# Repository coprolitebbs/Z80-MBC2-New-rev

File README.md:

# Z80-MBC2-New-rev
New revision of computer Z80-MBC2

4 blocks and Mainboard

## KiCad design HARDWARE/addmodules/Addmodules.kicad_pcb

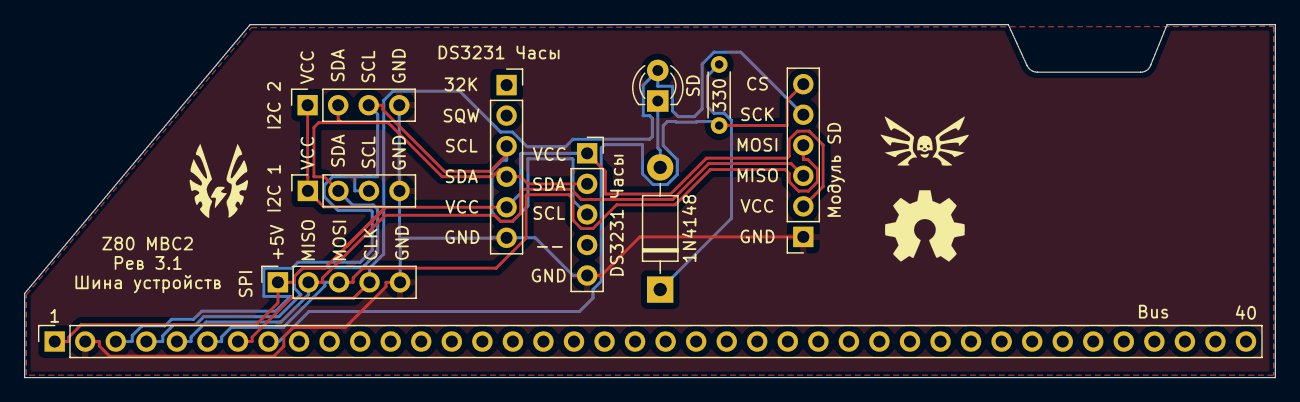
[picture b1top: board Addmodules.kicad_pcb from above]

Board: 2 copper layers, 104.0 x 29.3 mm, 10 parts (0 on the bottom side), 10 nets.

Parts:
D1: 1N4148; D_DO-41_SOD81_P10.16mm_Horizontal
D2: SD; LED_D3.0mm
J1: DS3231 Часы; PinSocket_1x06_P2.54mm_Vertical_RTC
J2: Модуль SD; PinSocket_1x06_P2.54mm_Vertical_SD
J3: DS3231 Часы; PinSocket_1x05_P2.54mm_Vertical
J4: I2C 1; PinSocket_1x04_P2.54mm_Vertical_I2C
J5: I2C 2; PinSocket_1x04_P2.54mm_Vertical_I2C
J6: SPI; PinSocket_1x05_P2.54mm_Vertical
J10: Bus; PinSocket_1x40_P2.54mm_Vertical
R1: 330; R_Axial_DIN0204_L3.6mm_D1.6mm_P5.08mm_Horizontal

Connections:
+5V: J1.5, J2.2, J3.1, J4.1, J5.1, J6.1, J10.1
CSK: D2.2 (A), J2.5, J6.4, J10.7
GND: J1.6, J2.1, J3.5, J4.4, J5.4, J6.5, J10.2
MISO: J2.3, J6.2, J10.5
MOSI: J2.4, J6.3, J10.6
unnamed: D1.1 (A), R1.1
unnamed: D1.2 (K), D2.1 (K)
SCL: J1.3, J3.3, J4.3, J5.3, J10.3
SDA: J1.4, J3.2, J4.2, J5.2, J10.4
SS: J2.6, J10.8, R1.2

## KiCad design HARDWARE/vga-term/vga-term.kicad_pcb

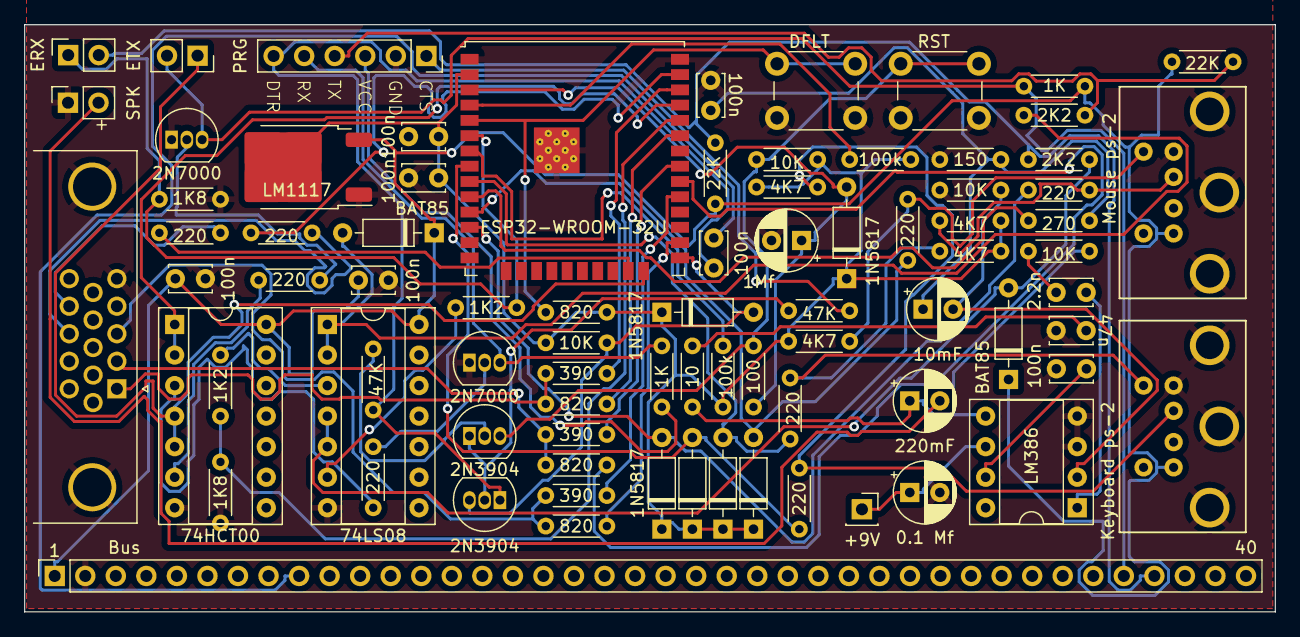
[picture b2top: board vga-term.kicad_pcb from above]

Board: 2 copper layers, 104.0 x 48.8 mm, 82 parts (0 on the bottom side), 62 nets.

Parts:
C1-nn1, C2, C3, C4, C5, C6, C11: 100n; C_Disc_D3.4mm_W2.1mm_P2.50mm
C8: 1Mf; CP_Radial_D5.0mm_P2.50mm
C9: 0.1 Mf; CP_Radial_D5.0mm_P2.50mm
C10: 10mF; CP_Radial_D5.0mm_P2.50mm
C12: 2.2n; C_Disc_D3.4mm_W2.1mm_P2.50mm
C13: 47n; C_Disc_D3.4mm_W2.1mm_P2.50mm
C18: 220mF; CP_Radial_D5.0mm_P2.50mm
D1, D2, D3, D4, D5, D6: 1N5817; D_DO-35_SOD27_P7.62mm_Horizontal
D7, D12: BAT85; D_DO-35_SOD27_P7.62mm_Horizontal
J1: DE15_Plug_HighDensity_MountingHoles; DSUB-15-HD_Female_Horizontal_P2.29x1.98mm_EdgePinOffset3.03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
J2: Mouse ps-2; MINI-DIN-6-FULL-SHIELD
J3: Keyboard ps-2; MINI-DIN-6-FULL-SHIELD
J5: PRG; PinSocket_1x06_P2.54mm_Vertical
J7: +9V; PinSocket_1x01_P2.54mm_Vertical
J8: SPK; PinSocket_1x02_P2.54mm_Vertical
J10: Bus; PinSocket_1x40_P2.54mm_Vertical
J11: ETX; PinSocket_1x02_P2.54mm_Vertical
J12: ERX; PinSocket_1x02_P2.54mm_Vertical
Q1, Q2: 2N3904; TO-92_Inline
Q3, Q4: 2N7000; TO-92_Inline
R1, R2, R9, R10, R14, R15, R28, R30: 220; R_Axial_DIN0204_L3.6mm_D1.6mm_P5.08mm_Horizontal
R3, R5, R7, R17: 820; R_Axial_DIN0204_L3.6mm_D1.6mm_P5.08mm_Horizontal
R4, R6, R8: 390; R_Axial_DIN0204_L3.6mm_D1.6mm_P5.08mm_Horizontal
R11, R12, R13, R16: 4K7; R_Axial_DIN0204_L3.6mm_D1.6mm_P5.08mm_Horizontal
R18: 100; R_Axial_DIN0204_L3.6mm_D1.6mm_P5.08mm_Horizontal
R19, R20: 47K; R_Axial_DIN0204_L3.6mm_D1.6mm_P5.08mm_Horizontal
R21, R22, R41, R42: 10K; R_Axial_DIN0204_L3.6mm_D1.6mm_P5.08mm_Horizontal
R23, R47: 2K2; R_Axial_DIN0204_L3.6mm_D1.6mm_P5.08mm_Horizontal
R24, R46: 22K; R_Axial_DIN0204_L3.6mm_D1.6mm_P5.08mm_Horizontal
R25, R49: 1K2; R_Axial_DIN0204_L3.6mm_D1.6mm_P5.08mm_Horizontal
R26, R48: 1K8; R_Axial_DIN0204_L3.6mm_D1.6mm_P5.08mm_Horizontal
R27, R29: 1K; R_Axial_DIN0204_L3.6mm_D1.6mm_P5.08mm_Horizontal
R39: 270; R_Axial_DIN0204_L3.6mm_D1.6mm_P5.08mm_Horizontal
R40: 150; R_Axial_DIN0204_L3.6mm_D1.6mm_P5.08mm_Horizontal
R43: 10; R_Axial_DIN0204_L3.6mm_D1.6mm_P5.08mm_Horizontal
R44, R45: 100k; R_Axial_DIN0204_L3.6mm_D1.6mm_P5.08mm_Horizontal
SW1: DFLT; SW_PUSH_6mm_H5mm
SW2: RST; SW_PUSH_6mm_H5mm
U1: ESP32-WROOM-32U
U2: LM1117; TO-252-2
U3: 74HCT00; DIP-14_W7.62mm_Socket
U4: 74LS08; DIP-14_W7.62mm_Socket
U6: LM386; DIP-8_W7.62mm_Socket

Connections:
+3.3V: C2.1, C3.2, D1.1 (K), D2.1 (K), D3.1 (K), D4.1 (K), D5.1 (K), D6.1 (K), R11.2, R12.2, R13.2, R16.2, R17.2, R21.1, R22.1, R44.1, R45.1, U1.2 (VDD), U2.2 (VO)
+5V: C5.1, C6.1, D7.1 (K), D12.1 (K), J2.4, J3.4, J10.1, R24.2, R29.1, R46.2, U2.3 (VI), U3.14 (VCC), U4.14 (VCC)
AUDIO: R39.1, U1.10 (IO25)
GND: C2.2, C3.1, C4.1, C5.2, C6.2, C8.2, C9.2, C11.1, C13.1, J1.0, J1.5, J1.6, J1.7, J1.8, J1.10, J2.3, J2.7, J3.3, J3.7, J5.2, J8.1, J10.2, Q3.1 (S), Q4.1 (S), R26.2, R40.1, R41.1, R48.2, SW1.1, SW2.1, U1.1 (GND), U1.15 (GND), U1.38 (GND), U1.39 (GND), U2.1 (GND), U3.7 (GND), U4.7 (GND), U6.3 (+), U6.4 (GND)
HSYNC: R2.1, U1.37 (IO23)
K_CLK: D3.2 (A), R14.1, U1.9 (IO33)
K_DAT: D4.2 (A), R15.1, U1.8 (IO32)
M_CLK: D2.2 (A), R9.1, U1.11 (IO26)
M_DAT: D1.2 (A), R10.1, U1.12 (IO27)
unnamed: C4.2, C10.1, R39.2, R40.2
unnamed: C12.1, R42.1
unnamed: C12.2, U6.1 (GAIN)
unnamed: C13.2, R43.2
unnamed: C18.1, R42.2, R43.1, U6.5
unnamed: C8.1, D5.2 (A), R18.1, U1.3 (EN)
unnamed: D6.2 (A), Q2.3 (C), R21.2, U1.25 (IO0)
unnamed: D7.2 (A), R23.2, U4.1, U4.2
unnamed: D12.2 (A), R47.2, U4.4, U4.5
unnamed: J1.13, R2.2
unnamed: J1.14, R1.2
unnamed: J2.1, R10.2, R12.1
unnamed: J2.5, R9.2, R11.1
unnamed: J3.1, R15.2, R16.1
unnamed: J3.5, R13.1, R14.2
unnamed: J5.1, R20.2
unnamed: C1-nn1.1, J5.6, Q2.1 (E), R19.1
unnamed: C9.1, J7.1, U6.6 (V+)
unnamed: C18.2, J8.2
unnamed: Q1.2 (B), R19.2
unnamed: Q1.3 (C), R18.2, R22.2, SW2.2
unnamed: Q1.1 (E), Q2.2 (B), R20.1
unnamed: Q3.2 (G), R28.2
unnamed: Q4.2 (G), R30.2
unnamed: R25.1, U4.3
unnamed: R28.1, U3.3
unnamed: R30.1, U3.6
unnamed: R49.1, U4.6
unnamed: R3.2, U1.26 (IO4)
unnamed: R4.2, U1.29 (IO5)
unnamed: R5.2, U1.30 (IO18)
unnamed: R6.2, U1.31 (IO19)
unnamed: R7.2, U1.33 (IO21)
unnamed: R8.2, U1.36 (IO22)
unnamed: R17.1, SW1.2, U1.5 (SENSOR_VN)
unnamed: C10.2, R41.2, U6.2 (-)
unnamed: C11.2, U6.7 (BYPASS)
RGB_B: J1.3, R3.1, R4.1
RGB_G: J1.2, R5.1, R6.1
RGB_R: J1.1, R7.1, R8.1
RST: C1-nn1.2, J10.9
RX: J10.37, J12.2, R46.1, R47.1
RX2: J12.1, R48.1, R49.2, U1.6 (IO34)
TX: J10.36, J11.2, Q4.3 (D), R29.2
TX2: J11.1, U1.24 (IO2), U3.4, U3.5
VSYNC: R1.1, U1.23 (IO15)
VUSB: J5.3, R27.1
_o_rx: U1.35 (TXD0/IO1), U3.1, U3.2
_o_tx: R25.2, R26.1, U1.34 (RXD0/IO3)
_p_rx: J5.5, Q3.3 (D), R27.2
_p_tx: J5.4, R23.1, R24.1
to4: R45.2, U1.4 (SENSOR_VP)
to7: R44.2, U1.7 (IO35)

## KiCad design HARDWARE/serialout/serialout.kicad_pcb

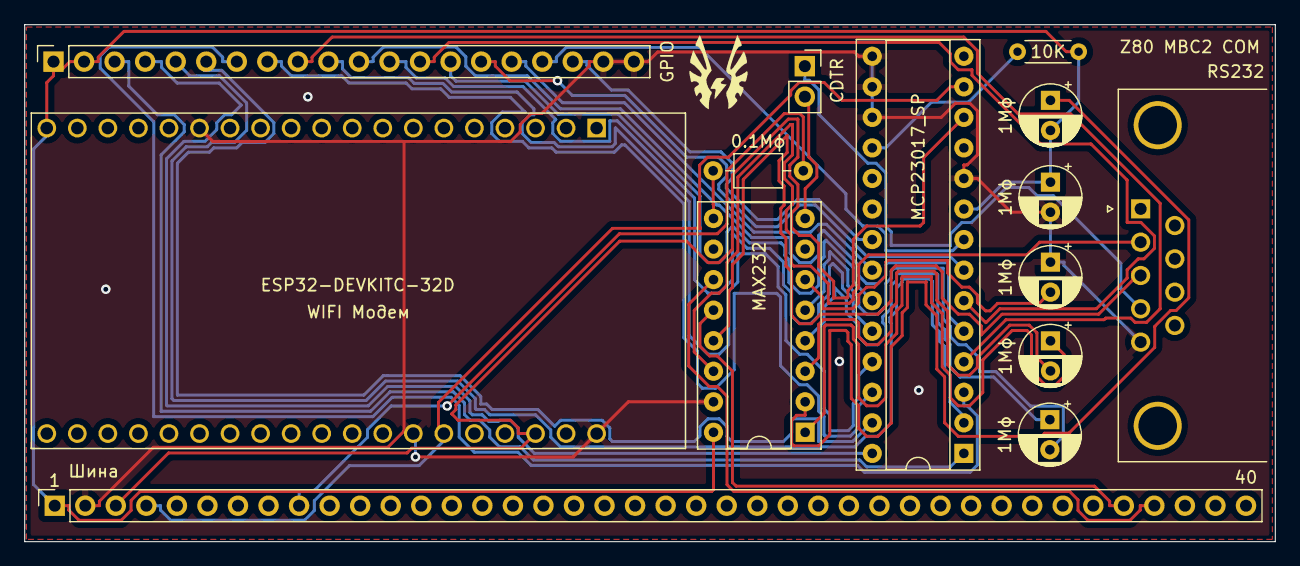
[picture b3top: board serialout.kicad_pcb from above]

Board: 2 copper layers, 104.0 x 43.0 mm, 14 parts (0 on the bottom side), 35 nets.

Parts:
C1, C3, C4, C5, C6: 1Mф; CP_Radial_D5.0mm_P2.50mm
C2: 0.1Mф; C_Axial_L3.8mm_D2.6mm_P7.50mm_Horizontal
J1: CDTR; PinSocket_1x02_P2.54mm_Vertical_POWER
J2: RS232; DSUB-9_Female_Horizontal_P2.77x2.84mm_EdgePinOffset7.70mm_H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
J3: GPIO; PinSocket_1x20_P2.54mm_Vertical
J10: Шина; PinSocket_1x40_P2.54mm_Vertical
R1: 10K; R_Axial_DIN0204_L3.6mm_D1.6mm_P5.08mm_Horizontal
U1: MAX232; DIP-16_W7.62mm_Socket
U2: MCP23017_SP; DIP-28_W7.62mm_Socket
U3: ESP32-DEVKITC-32D; MODULE_ESP32-DEVKITC-32D

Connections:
+5V: C3.1, C6.2, J3.1, J3.2, J10.1, R1.2, U1.16 (VCC), U2.9 (VDD), U3.19 (EXT_5V)
GND: C3.2, C5.1, J2.5, J3.19, J3.20, J10.2, U1.15 (GND), U2.10 (VSS), U2.15 (A0), U2.16 (A1), U2.17 (A2), U3.14 (GND1), U3.20 (GND3), U3.26 (GND2)
unnamed: C1.1, U1.1 (C1+)
unnamed: C1.2, U1.3 (C1-)
unnamed: C2.1, U1.9 (R2OUT)
unnamed: C4.1, U1.4 (C2+)
unnamed: C4.2, U1.5 (C2-)
unnamed: C5.2, U1.6 (VS-)
unnamed: C6.1, U1.2 (VS+)
unnamed: J1.1, J2.4
unnamed: J1.2, U1.8 (R2IN)
unnamed: J3.3, U2.1 (GPB0)
unnamed: J3.4, U2.28 (GPA7)
unnamed: J3.5, U2.2 (GPB1)
unnamed: J3.6, U2.27 (GPA6)
unnamed: J3.7, U2.3 (GPB2)
unnamed: J3.8, U2.26 (GPA5)
unnamed: J3.9, U2.4 (GPB3)
unnamed: J3.10, U2.25 (GPA4)
unnamed: J3.11, U2.5 (GPB4)
unnamed: J3.12, U2.24 (GPA3)
unnamed: J3.13, U2.6 (GPB5)
unnamed: J3.14, U2.23 (GPA2)
unnamed: J3.15, U2.7 (GPB6)
unnamed: J3.16, U2.22 (GPA1)
unnamed: J3.17, U2.8 (GPB7)
unnamed: J3.18, U2.21 (GPA0)
unnamed: R1.1, U2.18 (~RESET)
unnamed: J2.3, U1.13 (R1IN)
unnamed: J2.2, U1.14 (T1OUT)
RST: C2.2, J10.9
RX: J10.37, U1.11 (T1IN)
SCL: J10.3, U2.12 (SCK), U3.22 (IO22)
SDA: J10.4, U2.13 (SDA), U3.25 (IO21)
TX: J10.36, U1.12 (R1OUT)

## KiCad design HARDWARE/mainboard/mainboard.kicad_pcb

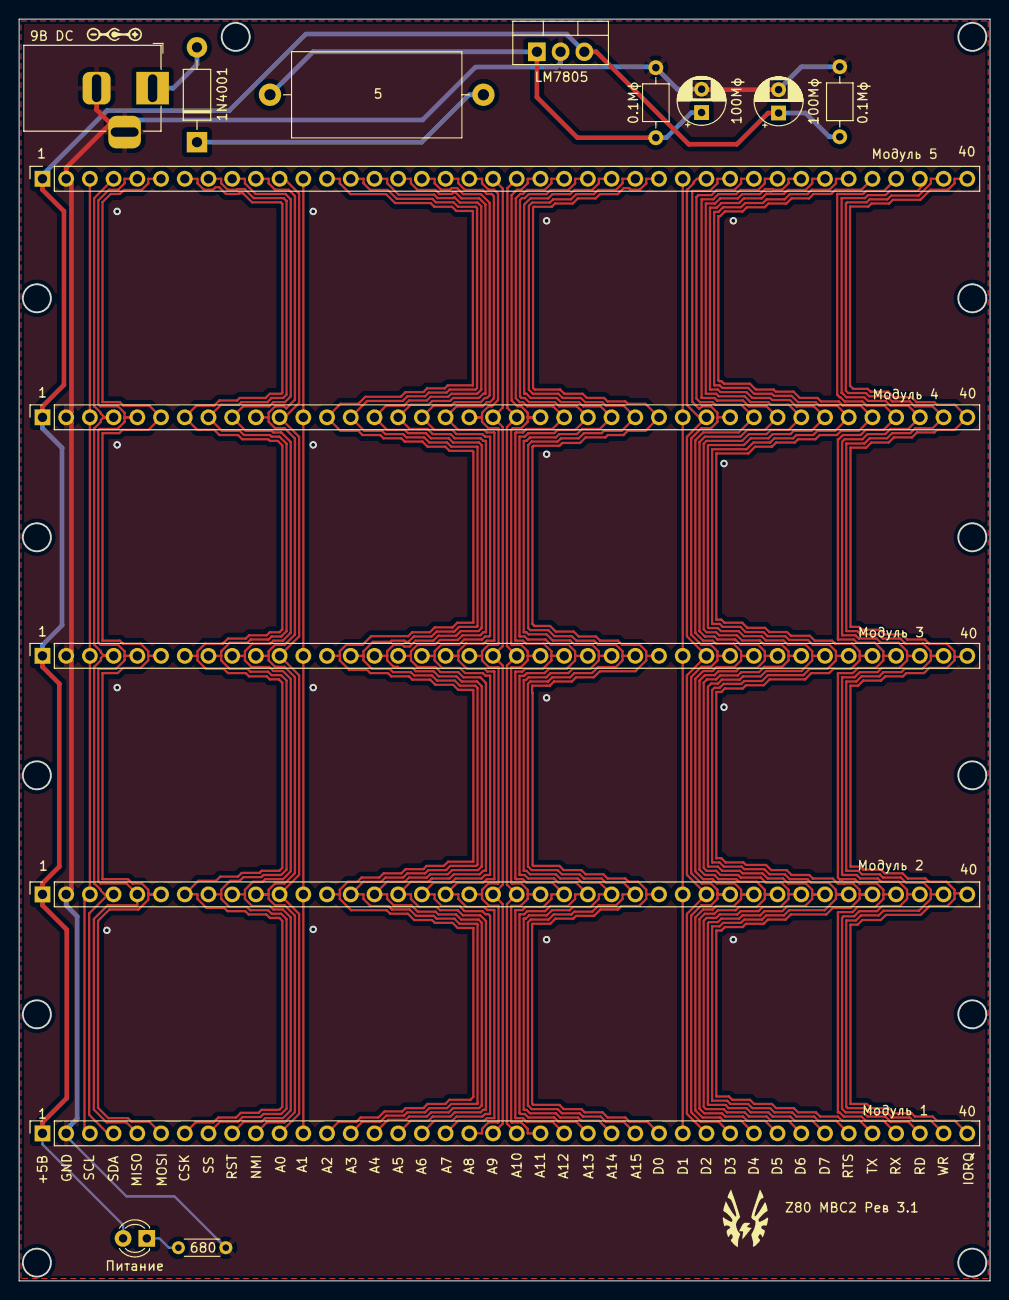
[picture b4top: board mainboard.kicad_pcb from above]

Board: 2 copper layers, 104.0 x 135.2 mm, 15 parts (0 on the bottom side), 44 nets.

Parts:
C1, C3: 100Мф; CP_Radial_D5.0mm_P2.50mm
C2, C4: 0.1Мф; C_Axial_L3.8mm_D2.6mm_P7.50mm_Horizontal
D1: 1N4001; D_DO-41_SOD81_P10.16mm_Horizontal
D2: Питание; LED_D3.0mm
J1: 9В DC; BarrelJack_Horizontal
J2: Модуль 2; PinSocket_1x40_P2.54mm_Vertical
J3: Модуль 3; PinSocket_1x40_P2.54mm_Vertical
J4: Модуль 4; PinSocket_1x40_P2.54mm_Vertical
J5: Модуль 5; PinSocket_1x40_P2.54mm_Vertical
J10: Модуль 1; PinSocket_1x40_P2.54mm_Vertical
R1: 680; R_Axial_DIN0204_L3.6mm_D1.6mm_P5.08mm_Horizontal
R2: 5; R_Axial_DIN0918_L18.0mm_D9.0mm_P22.86mm_Horizontal
U1: LM7805; TO-220-3_Vertical

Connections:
+5V: C3.1, C4.2, D2.2 (A), J2.1, J3.1, J4.1, J5.1, J10.1, U1.3 (VO)
A0: J2.11, J3.11, J4.11, J5.11, J10.11
A1: J2.12, J3.12, J4.12, J5.12, J10.12
A2: J2.13, J3.13, J4.13, J5.13, J10.13
A3: J2.14, J3.14, J4.14, J5.14, J10.14
A4: J2.15, J3.15, J4.15, J5.15, J10.15
A5: J2.16, J3.16, J4.16, J5.16, J10.16
A6: J2.17, J3.17, J4.17, J5.17, J10.17
A7: J2.18, J3.18, J4.18, J5.18, J10.18
A8: J2.19, J3.19, J4.19, J5.19, J10.19
A9: J2.20, J3.20, J4.20, J5.20, J10.20
A10: J2.21, J3.21, J4.21, J5.21, J10.21
A11: J2.22, J3.22, J4.22, J5.22, J10.22
A12: J2.23, J3.23, J4.23, J5.23, J10.23
A13: J2.24, J3.24, J4.24, J5.24, J10.24
A14: J2.25, J3.25, J4.25, J5.25, J10.25
A15: J2.26, J3.26, J4.26, J5.26, J10.26
CSK: J2.7, J3.7, J4.7, J5.7, J10.7
D0: J2.27, J3.27, J4.27, J5.27, J10.27
D1: J2.28, J3.28, J4.28, J5.28, J10.28
D2: J2.29, J3.29, J4.29, J5.29, J10.29
D3: J2.30, J3.30, J4.30, J5.30, J10.30
D4: J2.31, J3.31, J4.31, J5.31, J10.31
D5: J2.32, J3.32, J4.32, J5.32, J10.32
D6: J2.33, J3.33, J4.33, J5.33, J10.33
D7: J2.34, J3.34, J4.34, J5.34, J10.34
GND: C1.2, C2.1, C3.2, C4.1, J1.2, J1.3, J2.2, J3.2, J4.2, J5.2, J10.2, R1.1, U1.2 (GND)
IORQ: J2.40, J3.40, J4.40, J5.40, J10.40
MISO: J2.5, J3.5, J4.5, J5.5, J10.5
MOSI: J2.6, J3.6, J4.6, J5.6, J10.6
NMI: J2.10, J3.10, J4.10, J5.10, J10.10
unnamed: C1.1, C2.2, R2.1, U1.1 (VI)
unnamed: D1.1 (K), R2.2
unnamed: D1.2 (A), J1.1
unnamed: D2.1 (K), R1.2
RD: J2.38, J3.38, J4.38, J5.38, J10.38
RST: J2.9, J3.9, J4.9, J5.9, J10.9
RTS: J2.35, J3.35, J4.35, J5.35, J10.35
RX: J2.37, J3.37, J4.37, J5.37, J10.37
SCL: J2.3, J3.3, J4.3, J5.3, J10.3
SDA: J2.4, J3.4, J4.4, J5.4, J10.4
SS: J2.8, J3.8, J4.8, J5.8, J10.8
TX: J2.36, J3.36, J4.36, J5.36, J10.36
WR: J2.39, J3.39, J4.39, J5.39, J10.39

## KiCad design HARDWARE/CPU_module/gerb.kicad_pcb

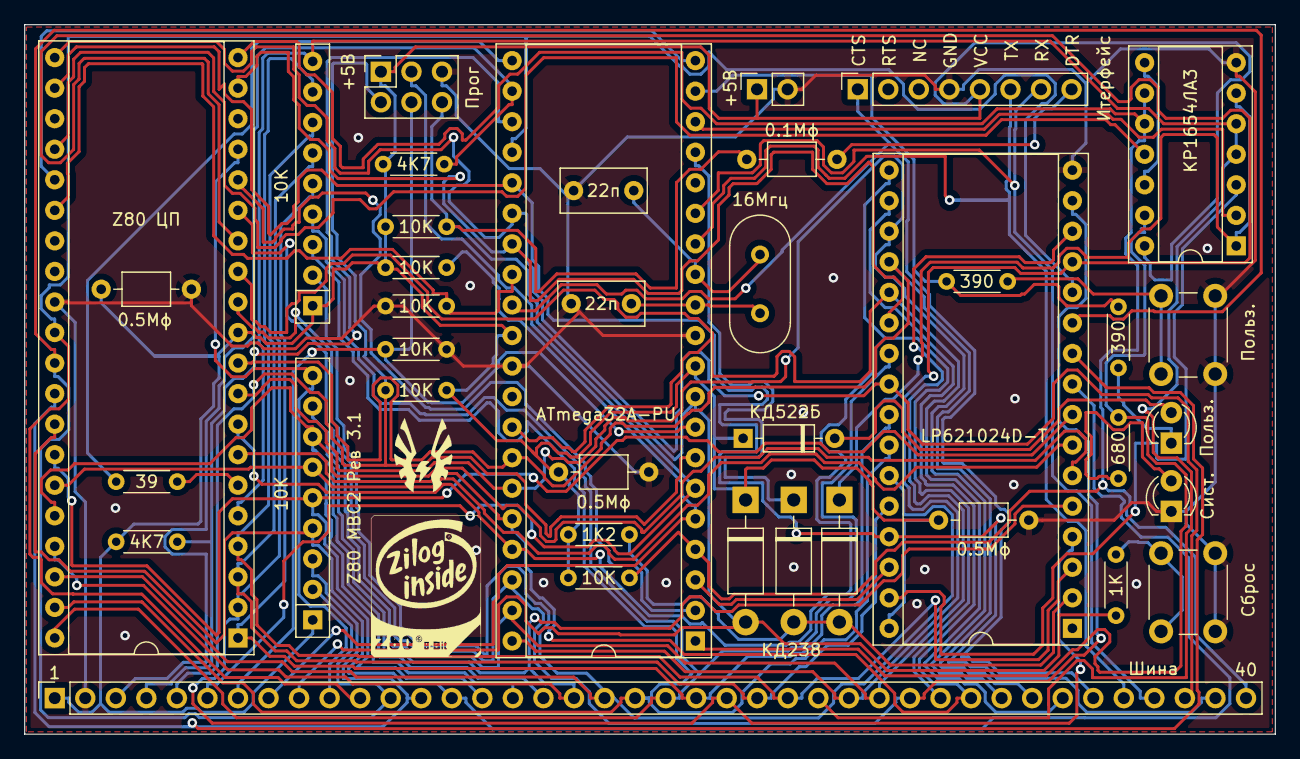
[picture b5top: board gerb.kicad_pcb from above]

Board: 2 copper layers, 104.0 x 59.0 mm, 40 parts (0 on the bottom side), 64 nets.

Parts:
C1, C2: 0.5Мф; C_Axial_L3.8mm_D2.6mm_P7.50mm_Horizontal
C3: 0.1Мф; C_Axial_L3.8mm_D2.6mm_P7.50mm_Horizontal
C4: 0.5Mф; C_Axial_L3.8mm_D2.6mm_P7.50mm_Horizontal
C5, C6: 22п; C_Rect_L7.0mm_W3.5mm_P5.00mm
D1: КД238; D_DO-41_SOD81_P10.16mm_Horizontal
D2, D3: 1N5817; D_DO-41_SOD81_P10.16mm_Horizontal
D4: Сист.; LED_D3.0mm
D8: Польз.; LED_D3.0mm
D9: КД522Б; D_DO-35_SOD27_P7.62mm_Horizontal
J1: Power; PinSocket_1x02_P2.54mm_Vertical_POWER
J2: Прог; PinSocket_2x03_P2.54mm_Vertical_ICSP
J4: Итерфейс; PinSocket_1x08_P2.54mm_Vertical_Serial
J10: Шина; PinSocket_1x40_P2.54mm_Vertical
R9, R11, R22, R25, R34, R35: 10K; R_Axial_DIN0204_L3.6mm_D1.6mm_P5.08mm_Horizontal
R10: 1K; R_Axial_DIN0204_L3.6mm_D1.6mm_P5.08mm_Horizontal
R20: 1K2; R_Axial_DIN0204_L3.6mm_D1.6mm_P5.08mm_Horizontal
R21: 680; R_Axial_DIN0204_L3.6mm_D1.6mm_P5.08mm_Horizontal
R26: 39; R_Axial_DIN0204_L3.6mm_D1.6mm_P5.08mm_Horizontal
R30, R32: 390; R_Axial_DIN0204_L3.6mm_D1.6mm_P5.08mm_Horizontal
R31, R33: 4K7; R_Axial_DIN0204_L3.6mm_D1.6mm_P5.08mm_Horizontal
REF1: z80-inside
RN1, RN2: 10K; R_Array_SIP9
SW1: Сброс; SW_PUSH_6mm_H5mm
SW2: Польз.; SW_PUSH_6mm_H5mm
U1: Z80 ЦП; DIP-40_W15.24mm_Socket
U2: КР1654ЛА3; DIP-14_W7.62mm_Socket
U3: ATmega32A-PU; DIP-40_W15.24mm_Socket
U4: LP621024D-T; DIP-32_W15.24mm_Socket
Y1: 16Mгц; Crystal_HC49-4H_Vertical

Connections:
+5V: C1.2, C2.1, C4.1, D1.1 (K), D9.1 (K), J1.1, J2.1 (VDD), J4.5, J10.1, R9.1, R11.1, R20.1, R22.2, R31.1, R33.1, R34.1, RN1.1 (common), RN2.1 (common), U1.11 (VCC), U2.14 (VCC), U3.10 (VCC), U3.30 (AVCC), U4.32 (VCC)
A0: J10.11, U1.30 (A0), U3.24 (PC2), U4.12 (A0)
A1: J10.12, RN1.2 (R1), U1.31 (A1), U4.11 (A1)
A2: J10.13, RN1.3 (R2), U1.32 (A2), U4.10 (A2)
A3: J10.14, RN1.4 (R3), U1.33 (A3), U4.9 (A3)
A4: J10.15, RN1.5 (R4), U1.34 (A4), U4.8 (A4)
A5: J10.16, RN1.6 (R5), U1.35 (A5), U4.7 (A5)
A6: J10.17, RN1.7 (R6), U1.36 (A6), U4.6 (A6)
A7: J10.18, RN1.8 (R7), U1.37 (A7), U4.5 (A7)
A8: J10.19, RN2.2 (R1), U1.38 (A8), U4.27 (A8)
A9: J10.20, RN2.3 (R2), U1.39 (A9), U4.26 (A9)
A10: J10.21, RN2.4 (R3), U1.40 (A10), U4.23 (A10)
A11: J10.22, RN2.5 (R4), U1.1 (A11), U4.25 (A11)
A12: J10.23, RN2.6 (R5), U1.2 (A12), U4.4 (A12)
A13: J10.24, RN2.7 (R6), U1.3 (A13), U4.28 (A13)
A14: J10.25, RN2.8 (R7), U1.4 (A14), U4.3 (A14)
A15: J10.26, RN2.9 (R8), U1.5 (A15), U2.4, U2.5
BUSREQ: U1.25 (~BUSRQ), U3.20 (PD6)
CSK: J2.4 (CSK), J10.7, R35.2, U3.8 (PB7)
D0: J10.27, U1.14 (D0), U3.40 (PA0), U4.13 (D0)
D1: J10.28, U1.15 (D1), U3.39 (PA1), U4.14 (D1)
D2: J10.29, U1.12 (D2), U3.38 (PA2), U4.15 (D2)
D3: J10.30, U1.8 (D3), U3.37 (PA3), U4.17 (D3)
D4: J10.31, U1.7 (D4), U3.36 (PA4), U4.18 (D4)
D5: J10.32, U1.9 (D5), U3.35 (PA5), U4.19 (D5)
D6: J10.33, U1.10 (D6), U3.34 (PA6), U4.20 (D6)
D7: J10.34, U1.13 (D7), U3.33 (PA7), U4.21 (D7)
GND: C1.1, C2.2, C4.2, C5.2, C6.2, D4.1 (K), J1.2, J2.5 (GND), J4.4, J10.2, R25.1, R35.1, SW1.2, SW2.2, U1.29 (GND), U2.7 (GND), U3.11 (GND), U3.31 (GND), U4.16 (GND)
INT: U1.16 (~INT), U3.2 (PB1)
IORQ: J10.40, R22.1, U1.20 (~IORQ), U2.9, U2.10, U3.4 (PB3)
MISO: J2.2 (MISO), J10.5, R34.2, U3.7 (PB6)
MOSI: J2.3 (MOSI), J10.6, U3.6 (PB5)
MREQ: U1.19 (~MREQ), U3.27 (PC5), U4.22 (CE1)
NMI: J10.10, RN1.9 (R8), U1.17 (~NMI)
unnamed: C3.1, J4.8
unnamed: C5.1, U3.13 (XTAL1), Y1.2
unnamed: C6.1, U3.12 (XTAL2), Y1.1
unnamed: D2.1 (K), U2.1, U2.6
unnamed: D2.2 (A), D3.2 (A), R20.2, U4.2 (A16)
unnamed: D4.2 (A), R21.1
unnamed: U2.8, U2.12
unnamed: D8.2 (A), D9.2 (A)
unnamed: R10.1, SW1.1
unnamed: R26.2, U1.6 (~CLK)
unnamed: R30.1, SW2.1
unnamed: D8.1 (K), R32.1
unnamed: U2.3, U4.31 (A15)
PB0: R21.2, U2.13, U3.1 (PB0)
PB2: U3.3 (PB2), U4.30 (CE2)
PCB6: R25.2, U1.26 (~RESET), U3.28 (PC6)
PD3: D3.1 (K), U3.17 (PD3)
PD4: U2.2, U3.18 (PD4)
PD7: R26.1, U3.21 (PD7)
RD: J10.38, U1.21 (~RD), U3.26 (PC4), U4.24 (OE)
RST: C3.2, D1.2 (A), J2.6 (RST), J10.9, R10.2, R11.2, U3.9 (~RESET)
RTS: J4.1, J10.35, U3.29 (PC7)
RX: J4.7, J10.37, U3.15 (PD1)
SCL: J10.3, R33.2, U3.22 (PC0)
SDA: J10.4, R31.2, U3.23 (PC1)
SS: J10.8, R9.2, U3.5 (PB4)
TX: J4.6, J10.36, U3.14 (PD0)
USR: R30.2, R32.2, U3.19 (PD5)
WAIT: U1.24 (~WAIT), U2.11
WR: J10.39, U1.22 (~WR), U3.25 (PC3), U4.29 (R/W)

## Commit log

2023-08-26 Add files via upload
    Modification of uTerm2-S: a multi-emulation color RS232 terminal:
    https://hackaday.io/project/181583-uterm2-s-a-multi-emulation-color-rs232-terminal
2023-12-27 Add files via upload
    Some fixes
